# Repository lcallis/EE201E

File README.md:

# EE201E
## Hello
### It is nice to meet you <3
### 😃

# EE201

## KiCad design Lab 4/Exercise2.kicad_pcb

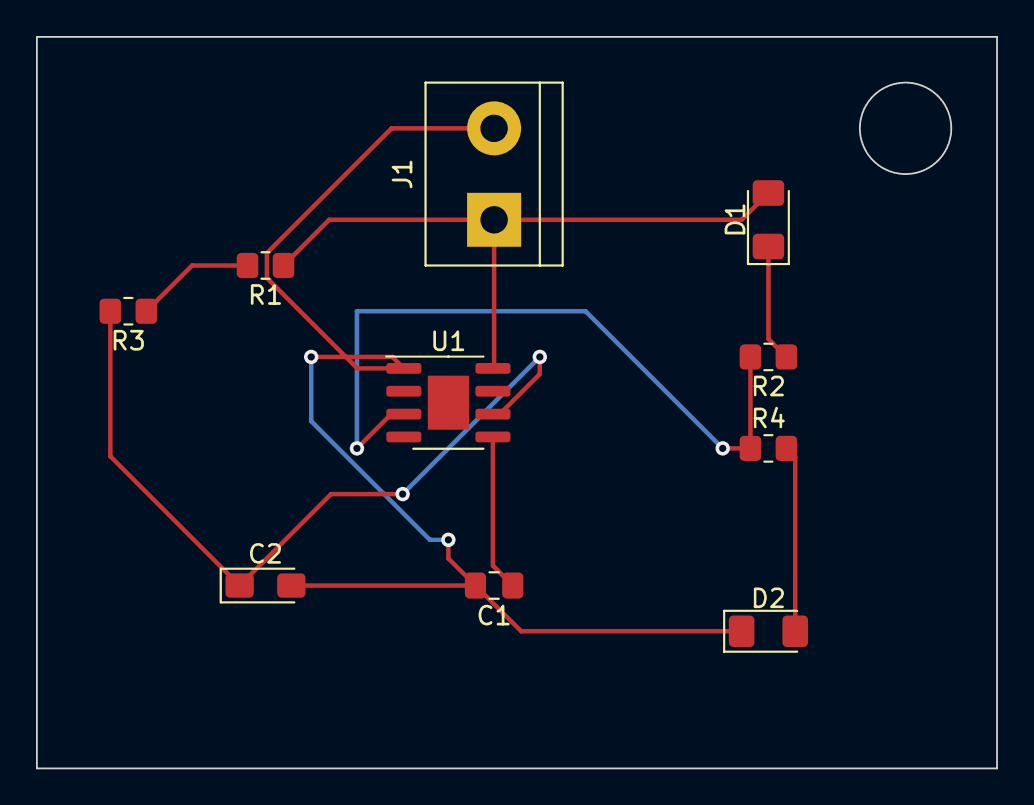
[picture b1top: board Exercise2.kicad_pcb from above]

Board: 2 copper layers, 53.3 x 40.6 mm, 10 parts (0 on the bottom side), 8 nets.

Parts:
C1: 0.01μF; C_0805_2012Metric_Pad1.18x1.45mm_HandSolder
C2: 10μF; CP_EIA-3216-18_Kemet-A_Pad1.58x1.35mm_HandSolder
D1, D2: LED; LED_1206_3216Metric_Pad1.42x1.75mm_HandSolder
J1: Conn_01x02_Male; TerminalBlock_bornier-2_P5.08mm
R1, R2, R4: 1k; R_0805_2012Metric_Pad1.20x1.40mm_HandSolder
R3: 10k; R_0805_2012Metric_Pad1.20x1.40mm_HandSolder
U1: NE555D; SOIC-8-1EP_3.9x4.9mm_P1.27mm_EP2.29x3mm

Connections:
+9V: D1.2 (A), J1.1, R1.1, U1.8 (VCC)
/pin_2: C2.1, R3.2, U1.6 (THR)
/pin_3: R2.2, R4.1, U1.3 (Q)
GND: C1.2, C2.2, D2.1 (K), J1.2, U1.1 (GND)
unnamed: C1.1, U1.5 (CV)
unnamed: D1.1 (K), R2.1
unnamed: D2.2 (A), R4.2
unnamed: R1.2, R3.1

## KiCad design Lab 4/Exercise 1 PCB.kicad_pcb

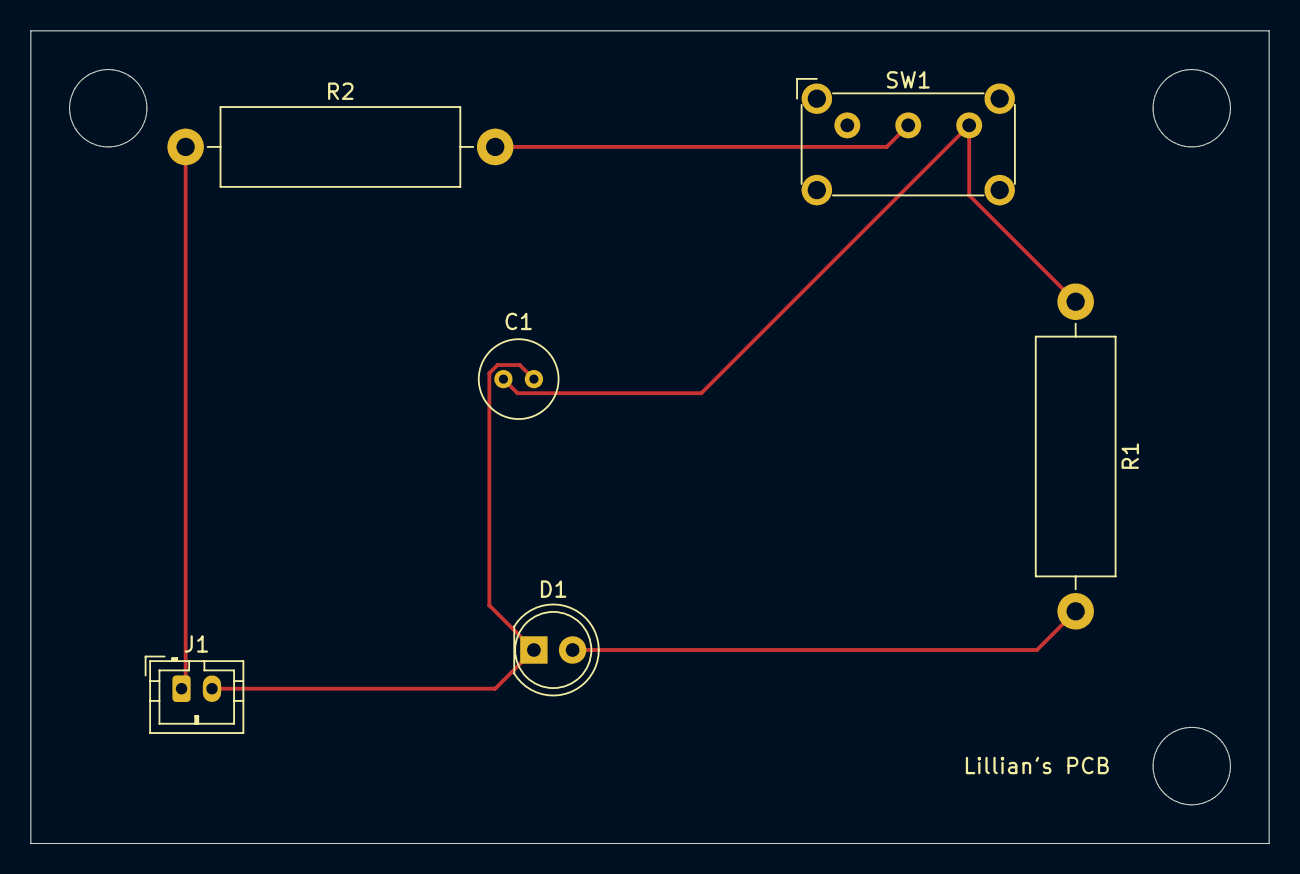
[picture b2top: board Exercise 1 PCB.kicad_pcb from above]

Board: 2 copper layers, 81.3 x 53.3 mm, 6 parts (0 on the bottom side), 5 nets.

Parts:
C1: 4.7 μF; C_Radial_D5.0mm_H5.0mm_P2.00mm
D1: LED; LED_D5.0mm
J1: 9 V; JST_PH_B2B-PH-K_1x02_P2.00mm_Vertical
R1: 20 kΩ; R_Axial_DIN0516_L15.5mm_D5.0mm_P20.32mm_Horizontal
R2: 2.2 kΩ; R_Axial_DIN0516_L15.5mm_D5.0mm_P20.32mm_Horizontal
SW1: SW_E-Switch_EG1224_SPDT_Angled

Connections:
unnamed: C1.1, R1.1, SW1.3 (C)
unnamed: C1.2, D1.1 (K), J1.2
unnamed: D1.2 (A), R1.2
unnamed: J1.1, R2.1
unnamed: R2.2, SW1.2 (B)

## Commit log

2023-01-14 Updating README
2023-01-14 Added a smiley :)
2023-01-14 Created README
2023-01-14 Initializing
2023-01-14 Initializing photo of Penny
2023-01-14 Initializing Penny
2023-01-14 Penny
2023-01-14 Adding emojis
2023-01-21 Uploading Arduino
2023-01-28 uploading
2023-02-04 commiting
2023-02-04 committing soldering
2023-02-17 committing
2023-03-11 finished
